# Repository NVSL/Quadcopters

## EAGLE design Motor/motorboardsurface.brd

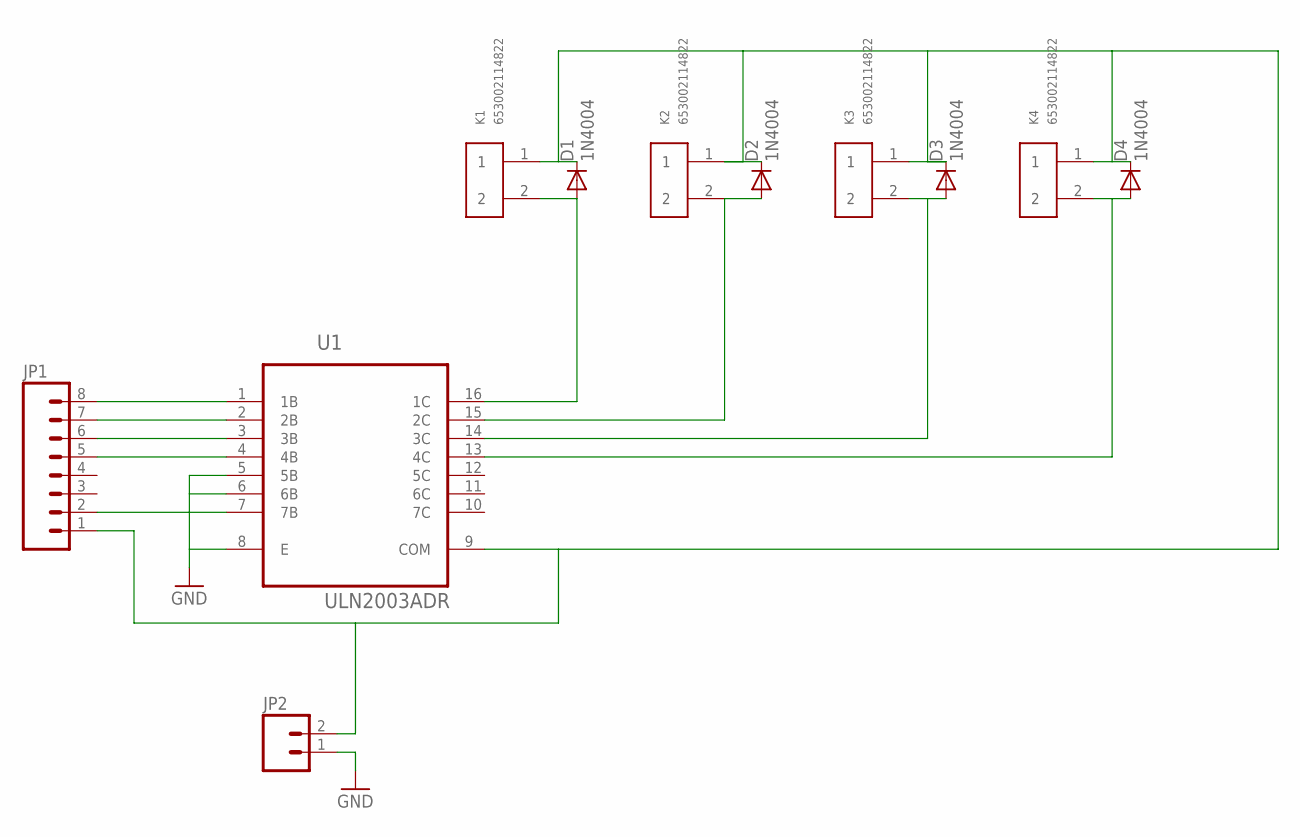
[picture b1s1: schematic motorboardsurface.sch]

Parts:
D1, D2, D3, D4: 1N4004; DO41-10; MPN 1N4004
JP1: M08NO_SILK_FEMALE_PTH; 1X08_NO_SILK
JP2: M02LOCK_LONGPADS; 1X02_LOCK_LONGPADS
K1, K2, K3, K4: 653002114822
U1: ULN2003ADR; SOIC127P600X175-16N

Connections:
GND: JP1.2, JP2.1, U1.5 (5B), U1.6 (6B), U1.7 (7B), U1.8 (E)
unnamed: D1.C, D2.C, D3.C, D4.C, JP1.1, JP2.2, K1.1, K2.1, K3.1, K4.1, U1.9 (COM)
unnamed: JP1.8, U1.1 (1B)
unnamed: JP1.7, U1.2 (2B)
unnamed: JP1.6, U1.3 (3B)
unnamed: JP1.5, U1.4 (4B)
unnamed: D1.A, K1.2, U1.16 (1C)
unnamed: D2.A, K2.2, U1.15 (2C)
unnamed: D3.A, K3.2, U1.14 (3C)
unnamed: D4.A, K4.2, U1.13 (4C)

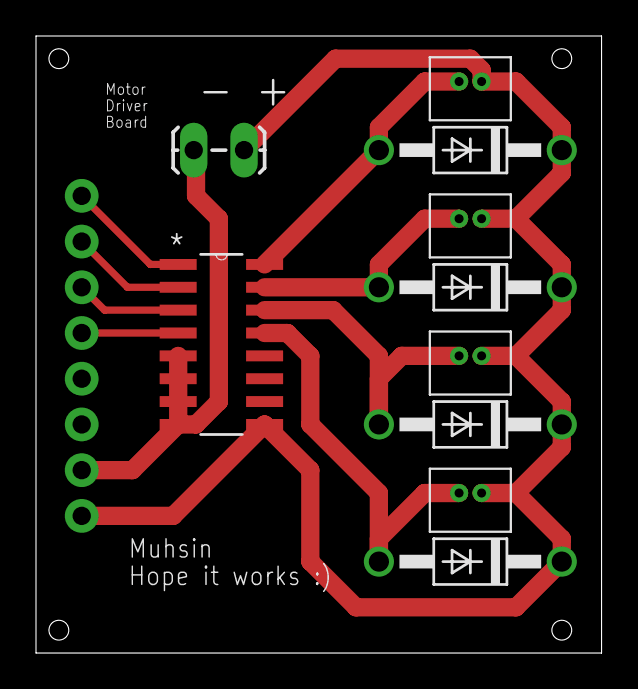
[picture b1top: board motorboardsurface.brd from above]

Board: 2 copper layers, 31.4 x 34.3 mm, 11 parts (0 on the bottom side), 10 nets.

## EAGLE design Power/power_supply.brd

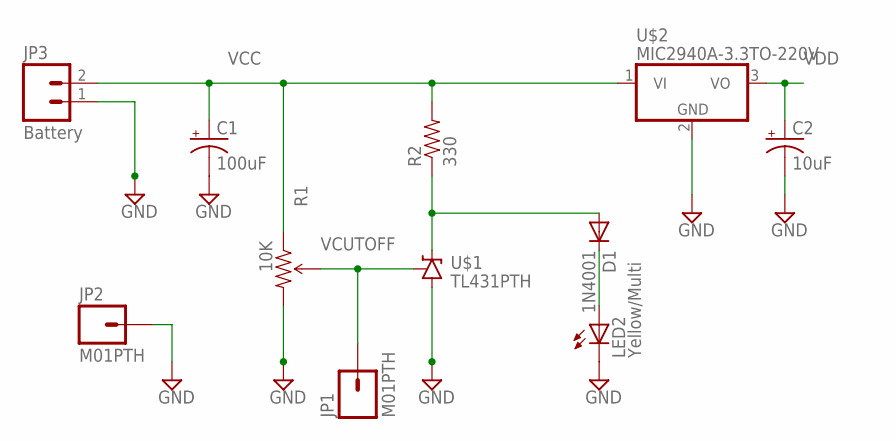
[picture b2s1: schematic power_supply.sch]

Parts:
C1: 100uF; E3,5-8
C2: 10uF; E2,5-5
D1: 1N4001; DO41-10
JP1, JP2: M01PTH; 1X01
JP3: Battery; 1X02
LED2: Yellow/Multi; LED5MM
R1: 10K; 3386U
R2: 330; AXIAL-0.3
U$1: TL431PTH; TO-92
U$2: MIC2940A-3.3TO-220V; TO-220V

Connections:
GND: C1.-, C2.-, JP2.1, JP3.1, LED2.K (C), R1.3 (CW), U$1.2 (A), U$2.2 (GND)
unnamed: D1.C, LED2.A
unnamed: D1.A, R2.P$1 (1), U$1.3 (C)
VCC: C1.+, JP3.2, R1.1 (CCW), R2.P$2 (2), U$2.1 (VI)
VCUTOFF: JP1.1, R1.2 (WIPER), U$1.1 (R)
VDD: C2.+, U$2.3 (VO)

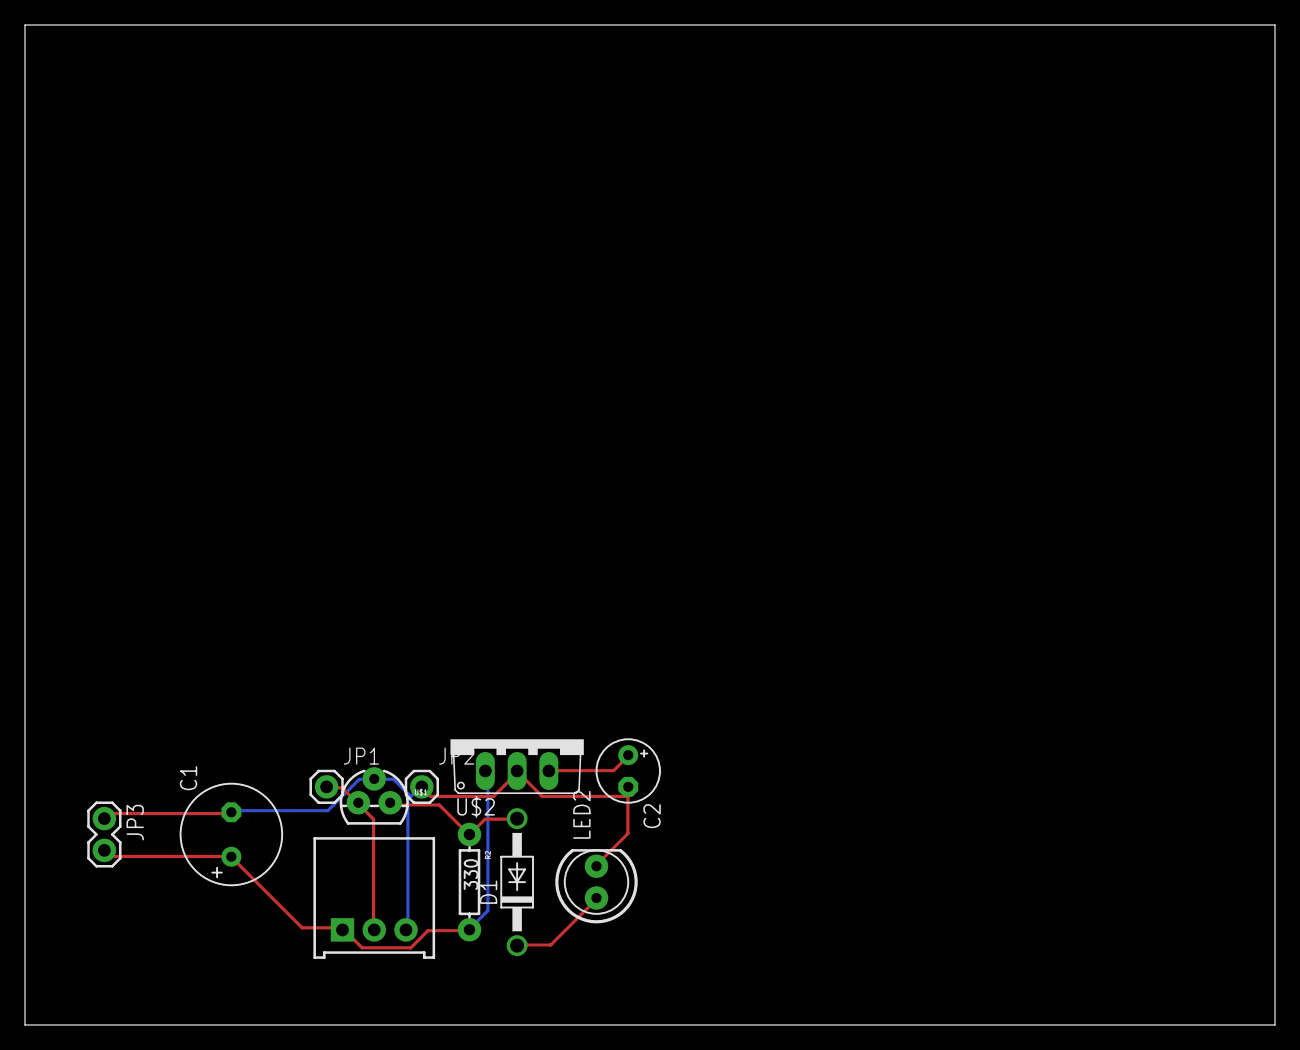
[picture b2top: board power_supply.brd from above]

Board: 2 copper layers, 100.0 x 80.0 mm, 11 parts (0 on the bottom side), 6 nets.

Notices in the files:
parts and their libraries:
SparkFun-Connectors: Licensing: Creative Commons ShareAlike 4.0 International - https://creativecommons.org/licenses/by-sa/4.0
Wuerth_Elektronik_eiCan_Wire_to_Board_Co: Copyright: Würth Elektronik
